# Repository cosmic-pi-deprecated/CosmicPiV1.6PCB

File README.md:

# CosmicPiV1.6
Version 1.6 of the Cosmic Pi, learning the lessons from V2 and going back to something simpler. All the components are now on a single PCB with a snap-off for the SiPM elements. We have also moved to KiCad!

# What do the signals do?

shapeout 1 & 2 - Shaped (i.e. amplified and stretched signal from the SiPMs - muon detection waveforms)

biasfb 1 & 2 - Feedback on the Vbias supply (i.e. to check that it's the right voltage)

inj led 1 & 2 - Light injector LEDs, allowing the operation of the SiPM to be checked (and calibrated) post-assembly

accint 1, 2 - Interrupts from the accelerometer, not really used for anything yet.

magint 3 - Interrupt from magnetometer

flag, boot0 - Signals to the Raspberry Pi, flag can be set by the STM32 to indicate a particular condition. Boot0 is used to set the boot mode of the STM32, for example when flashing.

vbusm otg dm otg dp - Vbus is the USB bus voltage detection line to the STM32 (i.e. in OTG mode, sense incoming voltage), DM and DP are the differential lines for USB communication.

swclk, swdio - These are the programming commands for the STM32, based on the ST-Link system.

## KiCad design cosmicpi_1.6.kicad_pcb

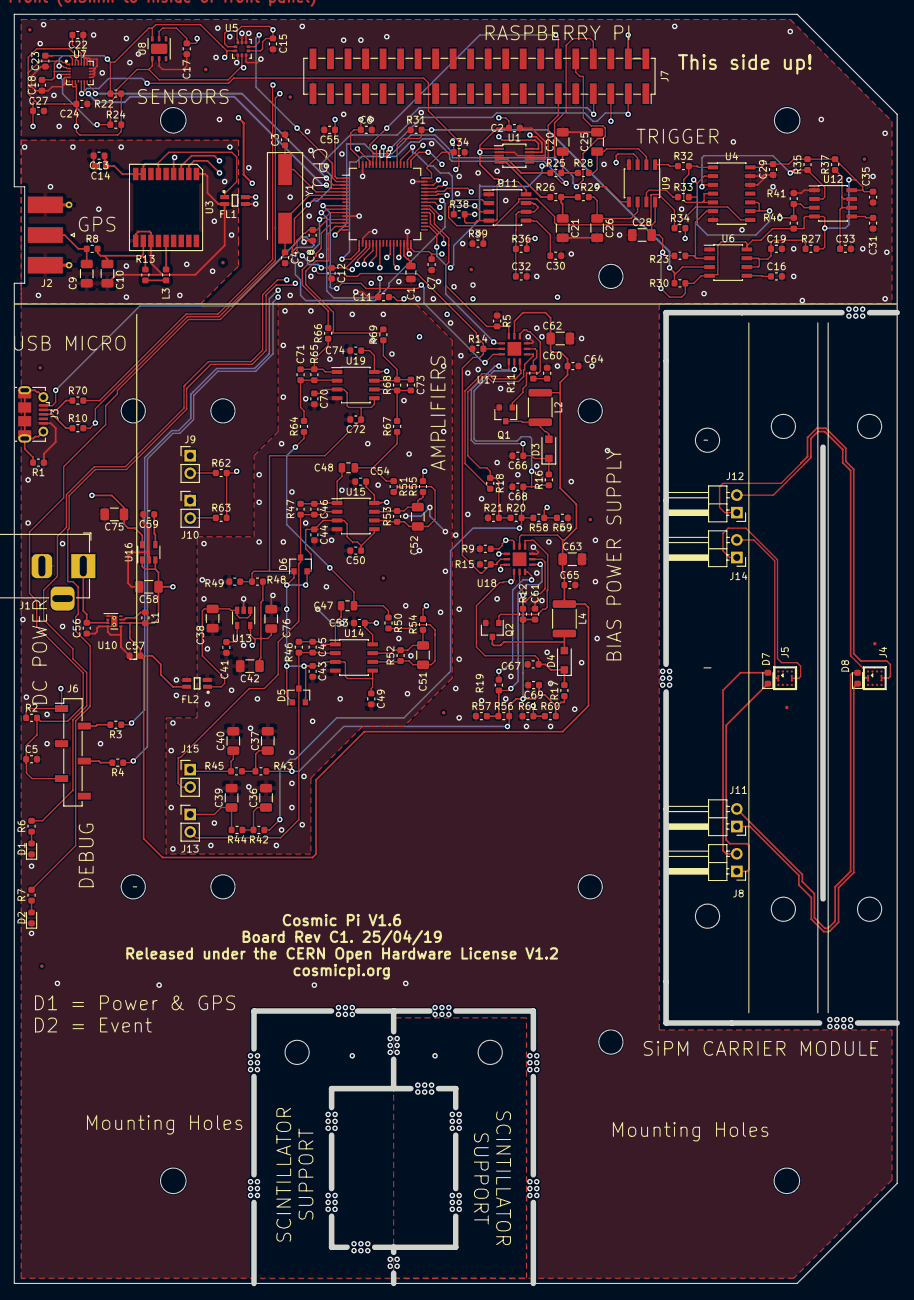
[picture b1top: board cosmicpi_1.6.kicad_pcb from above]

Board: 4 copper layers, 128.0 x 184.0 mm, 201 parts (0 on the bottom side), 131 nets.

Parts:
C1: 4.7u; C_0805_2012Metric
C2, C5, C6, C7, C8, C11, C12, C14, C15, C17, C18, C23, C27, C29, C34, C35, C43, C44, C49, C50, C53, C54, C55, C64, C65, C66, C67, C70, C72, C74: 100n; C_0603_1608Metric
C3, C4: 22p; C_0603_1608Metric
C9, C10, C51, C52: n.a.; C_1206_3216Metric
C13, C24, C56: 10u; C_0603_1608Metric
C16, C22, C30, C31, C41, C59: 10n; C_0603_1608Metric
C19, C32, C33, C60, C61: 220n; C_0603_1608Metric
C20, C21, C25, C26, C28, C36, C37, C38, C39, C40, C42, C58, C62, C63, C75: 1u; C_1206_3216Metric
C45, C46: 30p; C_0603_1608Metric
C47, C48: 100n; C_0805_2012Metric
C57: 22u; C_0603_1608Metric
C68, C69: 47n; C_0603_1608Metric
C71, C73: 1n; C_0603_1608Metric
C76: 100u; C_1206_3216Metric
D1, D2, D7, D8: LED; LED_0603_1608Metric
D3, D4: BAT46; D_SOD-123F
D5, D6: BAS70-04; SOT-23
FL1, FL2: EMI_Filter_LL_f; IND_744232090
H1, H2, H3, H3#2: MountingHole_3.7mm
J1: Barrel_Jack_Switch; BarrelJack_Horizontal
J2: SMA; SMA_Molex_73251-1153_EdgeMount_Horizontal
J3: USB_B_Micro; USB_Micro-B_Molex-105017-0001
J4, J5: Conn_01x04_Male; Ketek_PM3325-WB
J6: SWD; PinSocket_1x06_P2.54mm_Vertical_SMD_Pin1Left
J7: Raspberry_Pi_2_3; PinSocket_2x20_P2.54mm_Vertical_SMD
J8, J11, J12, J14: Conn_01x02_Male; PinHeader_1x02_P2.54mm_Horizontal
J9, J10, J13, J15: Conn_01x02_Female; PinHeader_1x02_P2.54mm_Vertical
L1: 2.2uH; L_0603_1608Metric
L2, L4: 150uH; L_1812_4532Metric
L3: 47nH; L_0603_1608Metric
Q1, Q2: BSS123; SOT-23
R1, R3, R4, R10, R70: 20; R_0603_1608Metric
R2, R30, R31, R38, R39, R40, R41: 100k; R_0603_1608Metric
R5, R9, R14, R15, R21, R22, R23, R24, R25, R26, R27, R28, R29, R34, R35, R36, R37, R49, R57, R59, R61: 10k; R_0603_1608Metric
R6, R7, R62, R63: 300; R_0603_1608Metric
R8: 0R; R_0603_1608Metric
R11, R12: 15k; R_0603_1608Metric
R13: 10; R_0603_1608Metric
R16, R17: 806; R_0603_1608Metric
R18, R19: 24.9k; R_0603_1608Metric
R20, R56, R58, R60: 200k; R_0603_1608Metric
R32, R33: 330R; R_0603_1608Metric
R42, R43, R44, R45, R50, R51: 1k; R_0603_1608Metric
R46, R47: 5100; R_0603_1608Metric
R48: 20k; R_0603_1608Metric
R52, R53: 30k; R_0603_1608Metric
R54, R55, R64, R66, R67, R69: 100; R_0603_1608Metric
R65, R68: 500k; R_0603_1608Metric
U1: MCP47CMB22; MSOP-10_3x3mm_P0.5mm
U2: STM32F401RETx; LQFP-64_10x10mm_P0.5mm
U3: L76-M33; LM76-M33
U4: 74HC00; SOIC-14_3.9x8.7mm_P1.27mm
U5: LPS25HB; ST_HLGA-10_2.5x2.5mm_P0.6mm_LayoutBorder3x2y
U6, U11, U12: LM555; SOIC-8_3.9x4.9mm_P1.27mm
U7: LSM9DS1; LGA-24L_3x3.5mm_P0.43mm
U8: SI7006-A20; DFN-6-1EP_3x3mm_P1mm_EP1.5x2.4mm
U9: MAX991; SOIC-8_3.9x4.9mm_P1.27mm
U10: TPS62163DSG; WSON-8-1EP_2x2mm_P0.5mm_EP0.9x1.6mm_ThermalVias
U13, U16: LP2985-3.3; SOT-23-5
U14, U15, U19: AD8039; SOIC-8_3.9x4.9mm_P1.27mm
U17, U18: MAX1932; QFN-12-1EP_4x4mm_P0.8mm
Y1: 8 MHz; Crystal_SMD_HC49-SD

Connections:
+3.3VA: C42.1, C53.1, C54.1, C74.1, C76.1, R48.1, U13.5, U14.8, U15.8, U19.8
+3V3: C2.2, C6.1, C7.1, C8.1, C11.1, C12.1, C15.2, C17.2, C18.2, C24.2, C27.1, C28.2, C29.2, C34.1, C35.1, C55.1, C75.1, FL1.2, J6.1, R2.1, R22.2, R23.2, R24.2, R27.2, R30.2, R34.2, R35.2, R36.2, R37.2, R38.2, R40.2, U1.1, U1.3, U2.1, U2.13, U2.19, U2.32, U2.48, U2.64, U4.14, U5.1, U5.6, U5.10, U6.4, U6.8, U7.1, U7.3, U7.7, U7.8, U7.22, U7.23, U8.5, U9.8, U11.4, U11.8, U12.4, U12.8, U16.5
+5V: C57.2, C58.1, C62.1, C63.1, C64.1, C65.1, FL2.2, J7.2, J7.4, L1.2, L2.1, L4.1, U10.6, U16.1, U16.3, U17.11, U18.11
/analog/SIGNAL_OUT_1: R54.2, U9.3
/analog/SIGNAL_OUT_2: R55.2, U9.5
ACC_INT1: U2.3, U7.12
ACC_INT2: U2.4, U7.11
BARO_INT: U2.2, U5.7
BIASFB1: R58.1, R59.2, U2.23
BIASFB2: R60.1, R61.2, U2.26
BOOT0: J7.12, U2.60
DAC0: R25.1, U1.4
DAC1: R26.1, U1.5
FLAG: J7.11, U2.27
GND: C1.2, C2.1, C3.2, C4.2, C5.2, C6.2, C7.2, C8.2, C11.2, C12.2, C15.1, C16.2, C17.1, C18.1, C19.2, C20.2, C21.2, C22.1, C23.1, C24.1, C25.2, C26.2, C27.2, C28.1, C29.1, C30.2, C31.2, C32.2, C33.2, C34.2, C35.2, C55.2, C56.1, C57.1, C58.2, C59.2, C60.2, C61.2, C62.2, C63.2, C64.2, C65.2, C66.2, C67.2, C68.2, C69.2, C75.2, D1.1, D2.1, FL1.3, FL2.3, J1.2, J3.5, J6.3, J7.6, J7.9, J7.14, J7.20, J7.25, J7.30, J7.34, J7.39, J9.1, J10.1, Q1.2, Q2.2, R1.1, R5.1, R9.1, R14.1, R15.1, R21.1, R31.1, R39.1, R41.1, R57.1, R59.1, R61.1, U1.2, U1.7, U1.8, U2.12, U2.18, U2.31, U2.47, U2.63, U4.7, U4.12, U4.13, U5.3, U5.5, U5.8, U5.9, U6.1, U7.5, U7.6, U7.14, U7.15, U7.16, U7.17, U7.18, U7.19, U7.20, U8.2, U9.4, U10.1, U10.4, U10.5, U10.9, U11.1, U12.1, U16.2, U17.9, U18.9
GNDD: C9.2, C10.2, C13.2, C14.2, FL1.4, J2.2, U3.1, U3.10, U3.12
GNDREF: C36.2, C37.2, C38.2, C39.2, C40.2, C41.2, C42.2, C43.2, C44.2, C49.2, C50.2, C53.2, C54.2, C70.2, C72.2, C74.2, C76.2, FL2.4, R49.2, U13.2, U14.4, U15.4, U19.4
GPSPPS: U2.50, U3.4
GPSRX: U2.58, U3.3
GPSTX: U2.43, U3.2
HVPSU_CL1: U2.9, U17.3
HVPSU_CL2: U2.10, U18.3
HVPSU_CS1: R5.2, U2.39, U17.12
HVPSU_CS2: R9.2, U2.38, U18.12
HVPSU_DIN: R14.2, R15.2, U2.11, U17.2, U18.2
HVPSU_SCLK: U2.34, U17.1, U18.1
INJ_LED1: R62.2, R63.2, U2.22
LED1: R6.2, U2.20
LED2: R7.2, U2.21
MAG_INT: U2.40, U7.10
unnamed: C1.1, U2.30
unnamed: C3.1, U2.5, Y1.1
unnamed: C4.1, U2.6, Y1.2
unnamed: C9.1, J2.1, R8.1
unnamed: C10.1, R8.2, R13.1, U3.11
unnamed: C13.1, C14.1, FL1.1, U3.6, U3.8, U3.9
unnamed: C16.1, U6.5
unnamed: C19.1, R27.1, U6.6, U6.7
unnamed: C20.1, R25.2, R28.1
unnamed: C21.1, R26.2, R29.1
unnamed: C22.2, U7.21
unnamed: C23.2, U7.24
unnamed: C25.1, R28.2, U9.2
unnamed: C26.1, R29.2, U9.6
unnamed: C30.1, U11.5
unnamed: C31.1, U12.5
unnamed: C32.1, R36.1, U11.6, U11.7
unnamed: C33.1, R37.1, U12.6, U12.7
unnamed: C36.1, R42.2, R44.1
unnamed: C37.1, R43.2, R45.1
unnamed: C38.1, FL2.1, U13.1, U13.3
unnamed: C39.1, J13.1, R44.2
unnamed: C40.1, J15.1, R45.2
unnamed: C41.1, U13.4
unnamed: C45.1, C47.2, R46.2, U14.1
unnamed: C45.2, D5.3, J13.2, R46.1, U14.2
unnamed: C46.1, C48.2, R47.2, U15.1
unnamed: C46.2, D6.3, J15.2, R47.1, U15.2
unnamed: C51.1, R52.2, R54.1, U14.7
unnamed: C51.2, R50.2, R52.1, U14.6
unnamed: C52.1, R53.2, R55.1, U15.7
unnamed: C52.2, R51.2, R53.1, U15.6
unnamed: C56.2, J1.1, U10.2, U10.3
unnamed: C59.1, U16.4
unnamed: C60.1, R11.2
unnamed: C61.1, R12.2
unnamed: C66.1, D3.1, R16.2, U17.4
unnamed: C67.1, D4.1, R17.2, U18.4
unnamed: C71.1, R65.2, R66.1, U19.1
unnamed: C71.2, R64.2, R65.1, U19.2
unnamed: C73.1, R68.2, R69.1, U19.7
unnamed: C73.2, R67.2, R68.1, U19.6
unnamed: D1.2, R6.1
unnamed: D2.2, R7.1
unnamed: D3.2, L2.2, Q1.3
unnamed: D4.2, L4.2, Q2.3
unnamed: D7.1, J8.1
unnamed: D7.2, J8.2
unnamed: D8.1, J11.1
unnamed: D8.2, J11.2
unnamed: J3.2, R70.1
unnamed: J3.3, R10.1
unnamed: J3.6, R1.2
unnamed: J6.2, R3.2
unnamed: J6.4, R4.2
unnamed: J9.2, R62.1
unnamed: J10.2, R63.1
unnamed: J4.3, J4.4, J12.1
unnamed: J4.1, J4.2, J12.2
unnamed: J5.3, J5.4, J14.1
unnamed: J5.1, J5.2, J14.2
unnamed: L1.1, U10.7
unnamed: L3.1, R13.2
unnamed: L3.2, U3.14
unnamed: Q1.1, U17.10
unnamed: Q2.1, U18.10
unnamed: R11.1, U17.8
unnamed: R12.1, U18.8
unnamed: R18.1, R20.1, R21.2, U17.7
unnamed: R18.2, U17.6
unnamed: R19.1, R56.1, R57.2, U18.7
unnamed: R19.2, U18.6
unnamed: R23.1, U4.6, U6.2
unnamed: R32.1, U9.1
unnamed: R33.1, U9.7
unnamed: R34.1, U4.8, U11.2
unnamed: R35.1, U4.3, U12.2
RX0: J7.8, U2.17
SCL0: R22.1, U1.9, U2.61, U5.2, U7.2, U8.6
SCL_SLAVE: J7.5, U2.41
SDA0: R24.1, U1.10, U2.59, U5.4, U7.4, U8.1
SDA_SLAVE: J7.3, U2.56
SHAPED_OUT_1: R66.2, U2.14
SHAPED_OUT_2: R69.2, U2.15
STRIGOUT_A: R30.1, R31.2, U2.53, U6.3
STRIGOUT_B: R38.1, R39.2, U2.52, U11.3
SWCLK: R3.1, U2.49
SWDIO: R4.1, U2.46
TAP1: C47.1, R50.1, R64.1
TAP2: C48.1, R51.1, R67.1
TRIG_A: R32.2, U4.1, U4.4, U4.5
TRIG_B: R33.2, U4.2, U4.9, U4.10
TRIG_OUT: R40.1, R41.2, U2.29, U12.3
TX0: J7.10, U2.16
USB_OTG_DM: R70.2, U2.44
USB_OTG_DP: R10.2, U2.45
USB_OTG_VBUS: J3.1, U2.42
VBIAS1: C68.1, R16.1, R20.2, R42.1, R58.2, U17.5
VBIAS2: C69.1, R17.1, R43.1, R56.2, R60.2, U18.5
V_OFFSET: C43.1, C44.1, C49.1, C50.1, C70.1, C72.1, D5.1, D5.2, D6.1, D6.2, R48.2, R49.1, U14.3, U14.5, U15.3, U15.5, U19.3, U19.5
_RESET: C5.1, J6.5, J7.7, R2.2, U2.7

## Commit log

2019-04-01 Uploaded everything. Created with KiCAD 5.1.0
2019-04-02 Updated bom
2019-04-02 corrected line numbers and MAX1932 package
2019-04-09 Updated board size to fit in housing
2019-04-14 Incorporated comments from TE-MPE
    They kindly checked the layout and schematic over for us! Can't be sure we got all the bugs until we build it though. Reversed raspberry pi header so that the connection will be inside the enclosure.
2019-04-24 Added some signal descriptions.
2019-04-25 Changed router width from .15 to .8mm
    feedback from Newbury Electronics who are manufacturing our first batch.
2019-04-25 added solder resist on underside
2019-04-26 BOM error in line 51 corrected.
2019-05-24 library updates with ketek footprint
2019-06-10 CubeMX file
2019-06-21 added pin 1 marks to MAX1932s on F.silk
2019-08-14 updated and added links

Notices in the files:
cosmicpi_1.6.kicad_pcb:
Released under the CERN Open Hardware License V1.2
